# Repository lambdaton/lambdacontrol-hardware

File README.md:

# LambdaControl - Hardware Files

This repository contains design and hardware related files for my DIY MIDI controller project [LambdaControl](https://www.lambdaton.de/diy-hardware/lambda-control/).

I designed and build LambdaControl for my upcoming live performance and decided to release all components under open source licenses, such that other artists can use my project as they like.

A complete documentation of the project can be found on my [website](https://www.lambdaton.de/diy-hardware/lambda-control/).

## Project Overview
LambdaControl is based on the [MIDIbox project](http://www.ucapps.de/), which provides a complete solution for basic tasks like reading analog and digital inputs (faders, knobs and encoders). However, the RGB button matrix of LambdaControl, which works like the matrix of a Novation Launchpad, required a complete custom development.

LambdaControl consists of the following parts: components from the MIDIbox project for the basic I/O and USB MIDI connection, separate microcontroller which controls the RGB matrix, and a MIDI Remote Script that connects the controller with Ableton Live over USB. Additionally, I created this repository for the hardware parts like the RGB button matrix PCB or the 3D printable case.

## Faceplate

This folder contains the vector drawing for the faceplate of LambdaControl. I manufactured the faceplate with a professional laser cutter at the [Fab Lab Aachen](http://hci.rwth-aachen.de/fablab) out of 3mm acrylic glass. This drawing is especially designed for my used linear/rotary potentiometers and encoders, such that adjustments would be needed if you want to use other components. I have chosen rotary potentiometers and encoders that are mounted to the faceplate with a nut, since this provides a really strong connection. The linear potentiometers are connected to the faceplate with a screw.

## Button Matrix PCB

This folder contains the PCB that I designed for the RGB button matrix of LambdaControl. The [button pads](https://www.sparkfun.com/products/7835) that I used for the matrix are from Sparkfun, such that I also used parts from their [Sparkfun Eagle Library](https://github.com/sparkfun/SparkFun-Eagle-Libraries) to design the PCB.

The matrix consists of 60 pads (10 columns, 6 rows). Every pad contains a 5mm RGB LED for the feedback and contacts to detect button presses. Connecting all this LEDs and buttons directly would require to much I/O pins, such that the PCB is designed for multiplexing. Multiplexing dramatically reduces the necessary I/O pins by connecting the pads in a matrix, such that the microcontroller can frequently iterate over the pins for the columns and rows to detect button presses and turn the LEDs on. More information about the implementation of the multiplexing can be found in the documentation.

## Case

Since I recently started with 3D printing as a new hobby, I decided to build the case of LambdaControl by using a 3D printer. The case has a dimension of 416.4mm x 276.4mm and was designed with Fusion 360. Every standard FDM 3D printer should be able to print the case. I printed mine in PLA. The only problem is the large size of the case, since most printer can normally just print objects with a maximal size of 215mm x 215mm. Therefore, I cut the case into six parts that can be printed separately. The solid connection between the parts is achieved by tongue and groove joints in the walls and bottom (thanks to my friend Henning for the tip).

Moreover, the case contains several mounting points for the different parts of LambdaControl like the faceplate or the PCBs. These mounting points are implemented by standard brass injection molding inserts that allow to securely attach the PCBs to the case.

## Button Pad Spacer

This folder contains the 3D model of the Button Pad Spacer that I designed to clamp the Sparkfun [button pads](https://www.sparkfun.com/products/7835) onto my button matrix PCB.

# License
The Faceplate, Case, and Button Pad Spacers are licensed under the MIT license. The Button Matrix PCB is licensed under the Creative Commons ShareAlike 4.0 International license, since it is based on parts from the [Sparkfun Eagle Libary](https://github.com/sparkfun/SparkFun-Eagle-Libraries).

## Author

2017 - LambdaTon

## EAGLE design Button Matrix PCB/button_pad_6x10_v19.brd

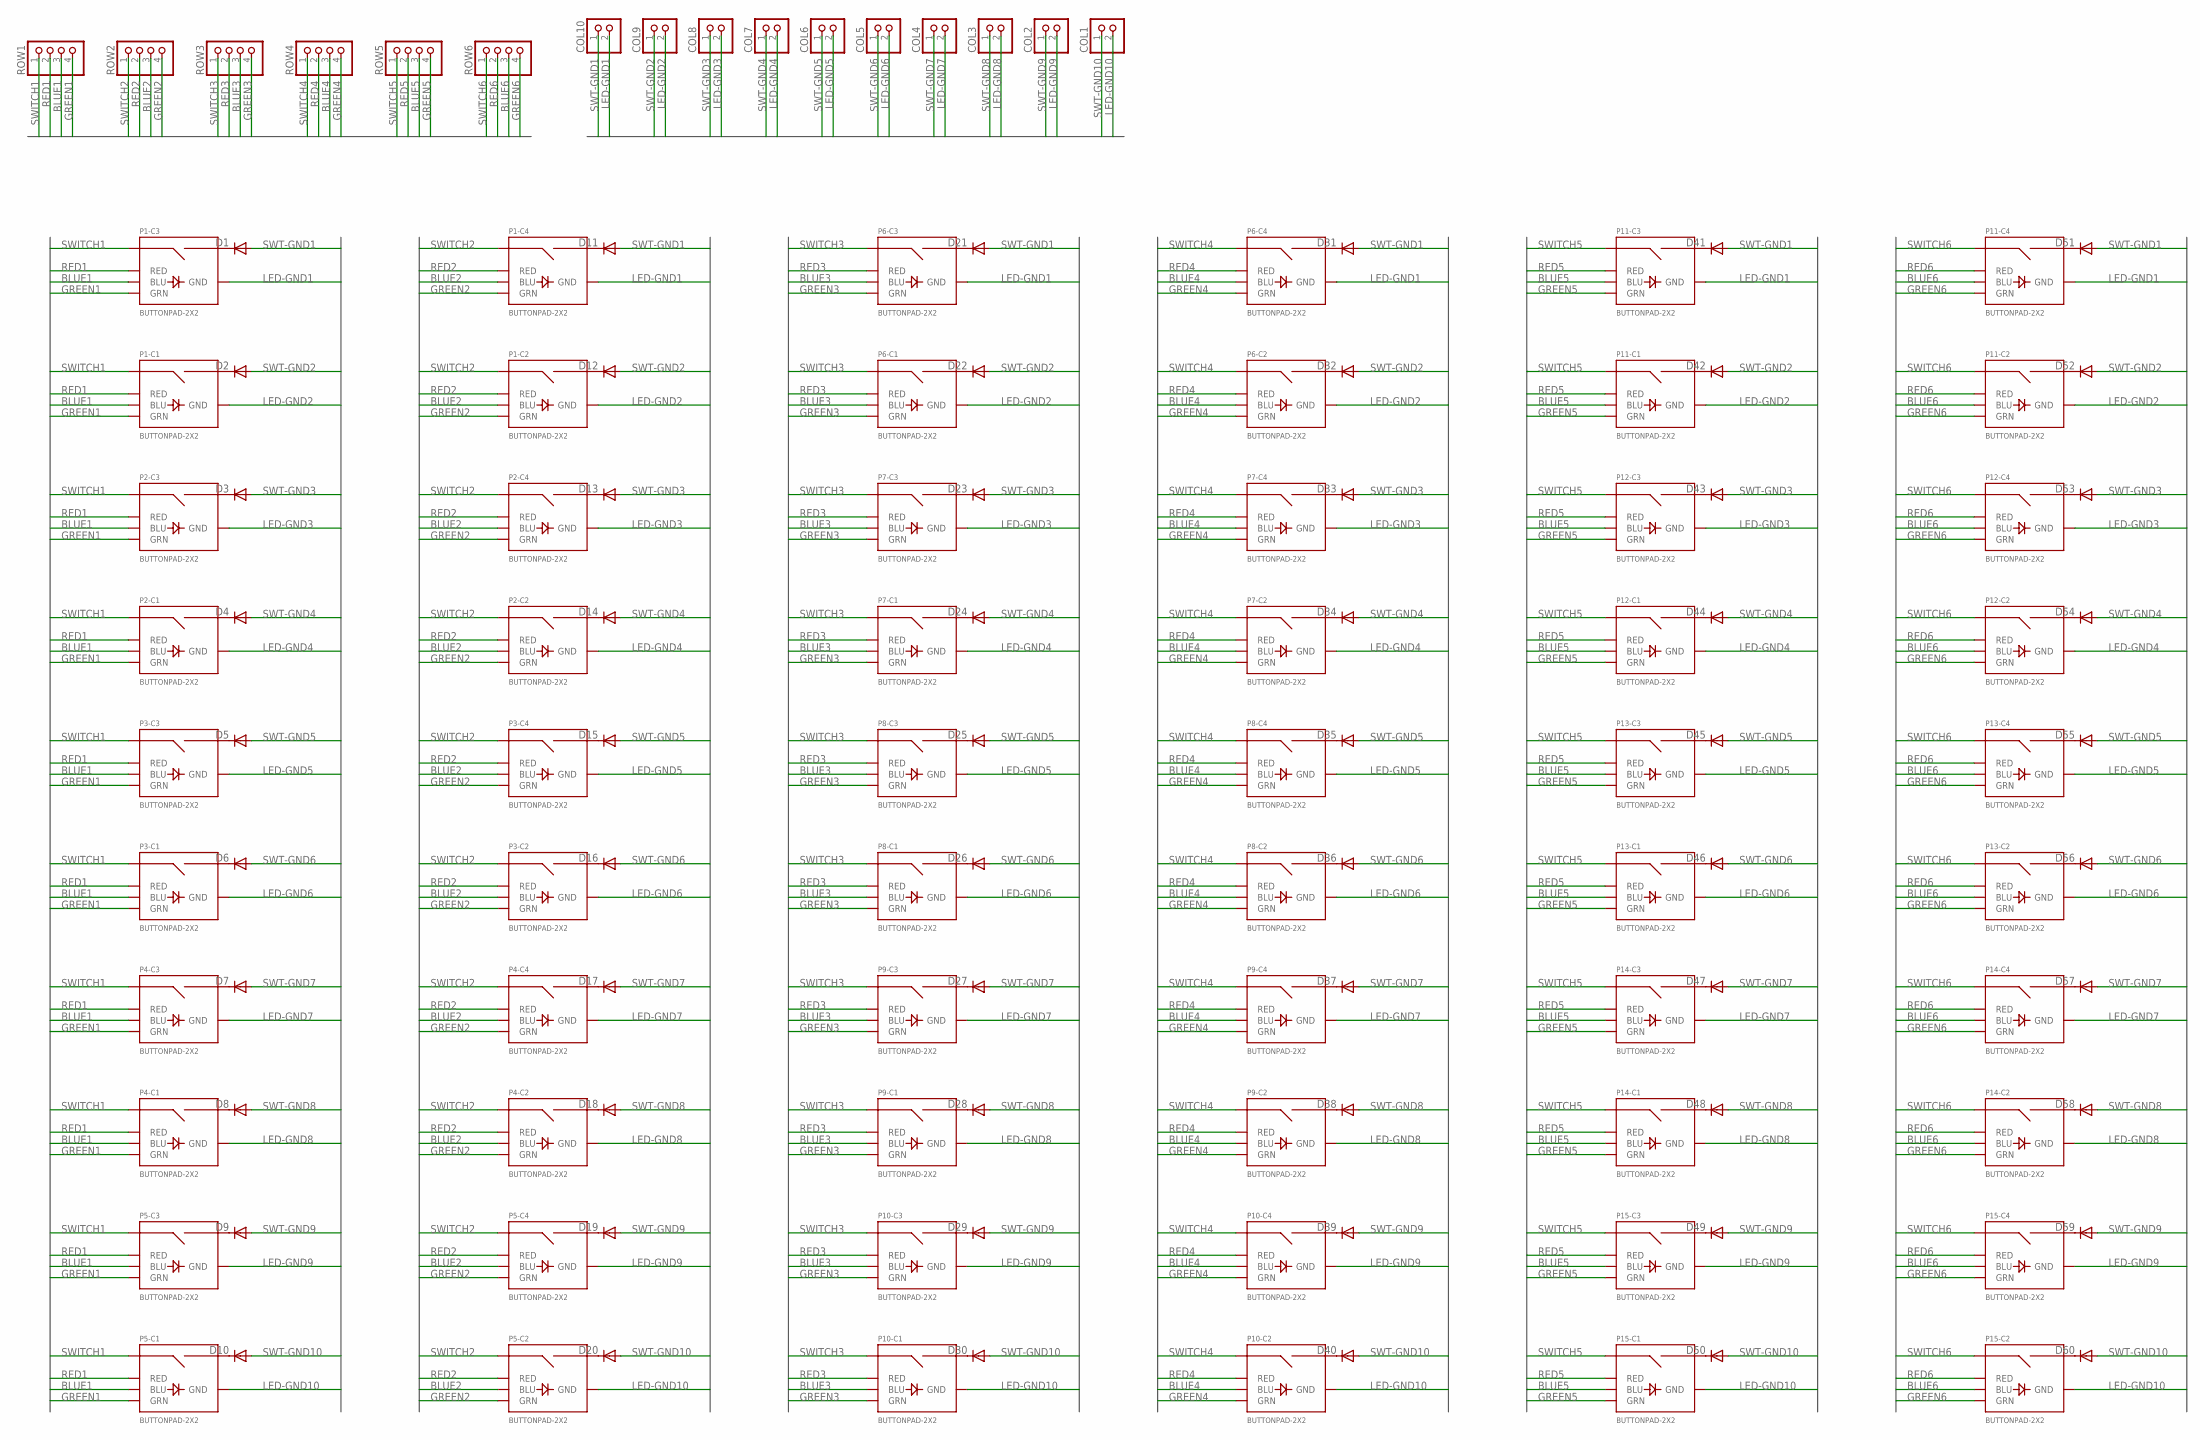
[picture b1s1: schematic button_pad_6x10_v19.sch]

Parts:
COL1, COL2, COL3, COL4, COL5, COL6, COL7, COL8, COL9, COL10: PINHD-1X2; 1X02
D1, D2, D3, D4, D5, D6, D7, D8, D9, D10, D11, D12, D13, D14, D15, D16, D17, D18, D19, D20, D21, D22, D23, D24, D25, D26, D27, D28, D29, D30, D31, D32, D33, D34, D35, D36, D37, D38, D39, D40, D41, D42, D43, D44, D45, D46, D47, D48, D49, D50, D51, D52, D53, D54, D55, D56, D57, D58, D59, D60: DIODE-1N4148; DOIDE-1N4148
P1, P2, P3, P4, P5, P6, P7, P8, P9, P10, P11, P12, P13, P14, P15: BUTTONPAD-2X2
ROW1, ROW2, ROW3, ROW4, ROW5, ROW6: PINHD-1X4; 1X04

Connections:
BLUE1: P1.BLU1 (BLU), P1.BLU3 (BLU), P2.BLU1 (BLU), P2.BLU3 (BLU), P3.BLU1 (BLU), P3.BLU3 (BLU), P4.BLU1 (BLU), P4.BLU3 (BLU), P5.BLU1 (BLU), P5.BLU3 (BLU), ROW1.3
BLUE2: P1.BLU2 (BLU), P1.BLU4 (BLU), P2.BLU2 (BLU), P2.BLU4 (BLU), P3.BLU2 (BLU), P3.BLU4 (BLU), P4.BLU2 (BLU), P4.BLU4 (BLU), P5.BLU2 (BLU), P5.BLU4 (BLU), ROW2.3
BLUE3: P6.BLU1 (BLU), P6.BLU3 (BLU), P7.BLU1 (BLU), P7.BLU3 (BLU), P8.BLU1 (BLU), P8.BLU3 (BLU), P9.BLU1 (BLU), P9.BLU3 (BLU), P10.BLU1 (BLU), P10.BLU3 (BLU), ROW3.3
BLUE4: P6.BLU2 (BLU), P6.BLU4 (BLU), P7.BLU2 (BLU), P7.BLU4 (BLU), P8.BLU2 (BLU), P8.BLU4 (BLU), P9.BLU2 (BLU), P9.BLU4 (BLU), P10.BLU2 (BLU), P10.BLU4 (BLU), ROW4.3
BLUE5: P11.BLU1 (BLU), P11.BLU3 (BLU), P12.BLU1 (BLU), P12.BLU3 (BLU), P13.BLU1 (BLU), P13.BLU3 (BLU), P14.BLU1 (BLU), P14.BLU3 (BLU), P15.BLU1 (BLU), P15.BLU3 (BLU), ROW5.3
BLUE6: P11.BLU2 (BLU), P11.BLU4 (BLU), P12.BLU2 (BLU), P12.BLU4 (BLU), P13.BLU2 (BLU), P13.BLU4 (BLU), P14.BLU2 (BLU), P14.BLU4 (BLU), P15.BLU2 (BLU), P15.BLU4 (BLU), ROW6.3
GREEN1: P1.GRN1 (GRN), P1.GRN3 (GRN), P2.GRN1 (GRN), P2.GRN3 (GRN), P3.GRN1 (GRN), P3.GRN3 (GRN), P4.GRN1 (GRN), P4.GRN3 (GRN), P5.GRN1 (GRN), P5.GRN3 (GRN), ROW1.4
GREEN2: P1.GRN2 (GRN), P1.GRN4 (GRN), P2.GRN2 (GRN), P2.GRN4 (GRN), P3.GRN2 (GRN), P3.GRN4 (GRN), P4.GRN2 (GRN), P4.GRN4 (GRN), P5.GRN2 (GRN), P5.GRN4 (GRN), ROW2.4
GREEN3: P6.GRN1 (GRN), P6.GRN3 (GRN), P7.GRN1 (GRN), P7.GRN3 (GRN), P8.GRN1 (GRN), P8.GRN3 (GRN), P9.GRN1 (GRN), P9.GRN3 (GRN), P10.GRN1 (GRN), P10.GRN3 (GRN), ROW3.4
GREEN4: P6.GRN2 (GRN), P6.GRN4 (GRN), P7.GRN2 (GRN), P7.GRN4 (GRN), P8.GRN2 (GRN), P8.GRN4 (GRN), P9.GRN2 (GRN), P9.GRN4 (GRN), P10.GRN2 (GRN), P10.GRN4 (GRN), ROW4.4
GREEN5: P11.GRN1 (GRN), P11.GRN3 (GRN), P12.GRN1 (GRN), P12.GRN3 (GRN), P13.GRN1 (GRN), P13.GRN3 (GRN), P14.GRN1 (GRN), P14.GRN3 (GRN), P15.GRN1 (GRN), P15.GRN3 (GRN), ROW5.4
GREEN6: P11.GRN2 (GRN), P11.GRN4 (GRN), P12.GRN2 (GRN), P12.GRN4 (GRN), P13.GRN2 (GRN), P13.GRN4 (GRN), P14.GRN2 (GRN), P14.GRN4 (GRN), P15.GRN2 (GRN), P15.GRN4 (GRN), ROW6.4
LED-GND1: COL10.2, P1.GND3 (GND), P1.GND4 (GND), P6.GND3 (GND), P6.GND4 (GND), P11.GND3 (GND), P11.GND4 (GND)
LED-GND2: COL9.2, P1.GND1 (GND), P1.GND2 (GND), P6.GND1 (GND), P6.GND2 (GND), P11.GND1 (GND), P11.GND2 (GND)
LED-GND3: COL8.2, P2.GND3 (GND), P2.GND4 (GND), P7.GND3 (GND), P7.GND4 (GND), P12.GND3 (GND), P12.GND4 (GND)
LED-GND4: COL7.2, P2.GND1 (GND), P2.GND2 (GND), P7.GND1 (GND), P7.GND2 (GND), P12.GND1 (GND), P12.GND2 (GND)
LED-GND5: COL6.2, P3.GND3 (GND), P3.GND4 (GND), P8.GND3 (GND), P8.GND4 (GND), P13.GND3 (GND), P13.GND4 (GND)
LED-GND6: COL5.2, P3.GND1 (GND), P3.GND2 (GND), P8.GND1 (GND), P8.GND2 (GND), P13.GND1 (GND), P13.GND2 (GND)
LED-GND7: COL4.2, P4.GND3 (GND), P4.GND4 (GND), P9.GND3 (GND), P9.GND4 (GND), P14.GND3 (GND), P14.GND4 (GND)
LED-GND8: COL3.2, P4.GND1 (GND), P4.GND2 (GND), P9.GND1 (GND), P9.GND2 (GND), P14.GND1 (GND), P14.GND2 (GND)
LED-GND9: COL2.2, P5.GND3 (GND), P5.GND4 (GND), P10.GND3 (GND), P10.GND4 (GND), P15.GND3 (GND), P15.GND4 (GND)
LED-GND10: COL1.2, P5.GND1 (GND), P5.GND2 (GND), P10.GND1 (GND), P10.GND2 (GND), P15.GND1 (GND), P15.GND2 (GND)
unnamed: D1.P$2 (C), P1.SIG6 (SIG2)
unnamed: D2.P$2 (C), P1.SIG2
unnamed: D3.P$2 (C), P2.SIG6 (SIG2)
unnamed: D4.P$2 (C), P2.SIG2
unnamed: D5.P$2 (C), P3.SIG6 (SIG2)
unnamed: D6.P$2 (C), P3.SIG2
unnamed: D16.P$2 (C), P3.SIG4 (SIG2)
unnamed: D15.P$2 (C), P3.SIG8 (SIG2)
unnamed: D14.P$2 (C), P2.SIG4 (SIG2)
unnamed: D13.P$2 (C), P2.SIG8 (SIG2)
unnamed: D12.P$2 (C), P1.SIG4 (SIG2)
unnamed: D11.P$2 (C), P1.SIG8 (SIG2)
unnamed: D7.P$2 (C), P4.SIG6 (SIG2)
unnamed: D8.P$2 (C), P4.SIG2
unnamed: D9.P$2 (C), P5.SIG6 (SIG2)
unnamed: D10.P$2 (C), P5.SIG2
unnamed: D21.P$2 (C), P6.SIG6 (SIG2)
unnamed: D22.P$2 (C), P6.SIG2
unnamed: D32.P$2 (C), P6.SIG4 (SIG2)
unnamed: D31.P$2 (C), P6.SIG8 (SIG2)
unnamed: D20.P$2 (C), P5.SIG4 (SIG2)
unnamed: D19.P$2 (C), P5.SIG8 (SIG2)
unnamed: D18.P$2 (C), P4.SIG4 (SIG2)
unnamed: D17.P$2 (C), P4.SIG8 (SIG2)
unnamed: D23.P$2 (C), P7.SIG6 (SIG2)
unnamed: D24.P$2 (C), P7.SIG2
unnamed: D33.P$2 (C), P7.SIG8 (SIG2)
unnamed: D34.P$2 (C), P7.SIG4 (SIG2)
unnamed: D30.P$2 (C), P10.SIG2
unnamed: D29.P$2 (C), P10.SIG6 (SIG2)
unnamed: D39.P$2 (C), P10.SIG8 (SIG2)
unnamed: D40.P$2 (C), P10.SIG4 (SIG2)
unnamed: D46.P$2 (C), P13.SIG2
unnamed: D45.P$2 (C), P13.SIG6 (SIG2)
unnamed: D55.P$2 (C), P13.SIG8 (SIG2)
unnamed: D56.P$2 (C), P13.SIG4 (SIG2)
unnamed: D47.P$2 (C), P14.SIG6 (SIG2)
unnamed: D48.P$2 (C), P14.SIG2
unnamed: D58.P$2 (C), P14.SIG4 (SIG2)
unnamed: D57.P$2 (C), P14.SIG8 (SIG2)
unnamed: D51.P$2 (C), P11.SIG8 (SIG2)
unnamed: D41.P$2 (C), P11.SIG6 (SIG2)
unnamed: D42.P$2 (C), P11.SIG2
unnamed: D52.P$2 (C), P11.SIG4 (SIG2)
unnamed: D25.P$2 (C), P8.SIG6 (SIG2)
unnamed: D35.P$2 (C), P8.SIG8 (SIG2)
unnamed: D36.P$2 (C), P8.SIG4 (SIG2)
unnamed: D26.P$2 (C), P8.SIG2
unnamed: D27.P$2 (C), P9.SIG6 (SIG2)
unnamed: D28.P$2 (C), P9.SIG2
unnamed: D37.P$2 (C), P9.SIG8 (SIG2)
unnamed: D38.P$2 (C), P9.SIG4 (SIG2)
unnamed: D43.P$2 (C), P12.SIG6 (SIG2)
unnamed: D44.P$2 (C), P12.SIG2
unnamed: D53.P$2 (C), P12.SIG8 (SIG2)
unnamed: D54.P$2 (C), P12.SIG4 (SIG2)
unnamed: D50.P$2 (C), P15.SIG2
unnamed: D49.P$2 (C), P15.SIG6 (SIG2)
unnamed: D59.P$2 (C), P15.SIG8 (SIG2)
unnamed: D60.P$2 (C), P15.SIG4 (SIG2)
RED1: P1.RED1 (RED), P1.RED3 (RED), P2.RED1 (RED), P2.RED3 (RED), P3.RED1 (RED), P3.RED3 (RED), P4.RED1 (RED), P4.RED3 (RED), P5.RED1 (RED), P5.RED3 (RED), ROW1.2
RED2: P1.RED2 (RED), P1.RED4 (RED), P2.RED2 (RED), P2.RED4 (RED), P3.RED2 (RED), P3.RED4 (RED), P4.RED2 (RED), P4.RED4 (RED), P5.RED2 (RED), P5.RED4 (RED), ROW2.2
RED3: P6.RED1 (RED), P6.RED3 (RED), P7.RED1 (RED), P7.RED3 (RED), P8.RED1 (RED), P8.RED3 (RED), P9.RED1 (RED), P9.RED3 (RED), P10.RED1 (RED), P10.RED3 (RED), ROW3.2
RED4: P6.RED2 (RED), P6.RED4 (RED), P7.RED2 (RED), P7.RED4 (RED), P8.RED2 (RED), P8.RED4 (RED), P9.RED2 (RED), P9.RED4 (RED), P10.RED2 (RED), P10.RED4 (RED), ROW4.2
RED5: P11.RED1 (RED), P11.RED3 (RED), P12.RED1 (RED), P12.RED3 (RED), P13.RED1 (RED), P13.RED3 (RED), P14.RED1 (RED), P14.RED3 (RED), P15.RED1 (RED), P15.RED3 (RED), ROW5.2
RED6: P11.RED2 (RED), P11.RED4 (RED), P12.RED2 (RED), P12.RED4 (RED), P13.RED2 (RED), P13.RED4 (RED), P14.RED2 (RED), P14.RED4 (RED), P15.RED2 (RED), P15.RED4 (RED), ROW6.2
SWITCH1: P1.SIG1, P1.SIG5 (SIG1), P2.SIG1, P2.SIG5 (SIG1), P3.SIG1, P3.SIG5 (SIG1), P4.SIG1, P4.SIG5 (SIG1), P5.SIG1, P5.SIG5 (SIG1), ROW1.1
SWITCH2: P1.SIG3 (SIG1), P1.SIG7 (SIG1), P2.SIG3 (SIG1), P2.SIG7 (SIG1), P3.SIG3 (SIG1), P3.SIG7 (SIG1), P4.SIG3 (SIG1), P4.SIG7 (SIG1), P5.SIG3 (SIG1), P5.SIG7 (SIG1), ROW2.1
SWITCH3: P6.SIG1, P6.SIG5 (SIG1), P7.SIG1, P7.SIG5 (SIG1), P8.SIG1, P8.SIG5 (SIG1), P9.SIG1, P9.SIG5 (SIG1), P10.SIG1, P10.SIG5 (SIG1), ROW3.1
SWITCH4: P6.SIG3 (SIG1), P6.SIG7 (SIG1), P7.SIG3 (SIG1), P7.SIG7 (SIG1), P8.SIG3 (SIG1), P8.SIG7 (SIG1), P9.SIG3 (SIG1), P9.SIG7 (SIG1), P10.SIG3 (SIG1), P10.SIG7 (SIG1), ROW4.1
SWITCH5: P11.SIG1, P11.SIG5 (SIG1), P12.SIG1, P12.SIG5 (SIG1), P13.SIG1, P13.SIG5 (SIG1), P14.SIG1, P14.SIG5 (SIG1), P15.SIG1, P15.SIG5 (SIG1), ROW5.1
SWITCH6: P11.SIG3 (SIG1), P11.SIG7 (SIG1), P12.SIG3 (SIG1), P12.SIG7 (SIG1), P13.SIG3 (SIG1), P13.SIG7 (SIG1), P14.SIG3 (SIG1), P14.SIG7 (SIG1), P15.SIG3 (SIG1), P15.SIG7 (SIG1), ROW6.1
SWT-GND1: COL10.1, D1.P$1 (A), D11.P$1 (A), D21.P$1 (A), D31.P$1 (A), D41.P$1 (A), D51.P$1 (A)
SWT-GND2: COL9.1, D2.P$1 (A), D12.P$1 (A), D22.P$1 (A), D32.P$1 (A), D42.P$1 (A), D52.P$1 (A)
SWT-GND3: COL8.1, D3.P$1 (A), D13.P$1 (A), D23.P$1 (A), D33.P$1 (A), D43.P$1 (A), D53.P$1 (A)
SWT-GND4: COL7.1, D4.P$1 (A), D14.P$1 (A), D24.P$1 (A), D34.P$1 (A), D44.P$1 (A), D54.P$1 (A)
SWT-GND5: COL6.1, D5.P$1 (A), D15.P$1 (A), D25.P$1 (A), D35.P$1 (A), D45.P$1 (A), D55.P$1 (A)
SWT-GND6: COL5.1, D6.P$1 (A), D16.P$1 (A), D26.P$1 (A), D36.P$1 (A), D46.P$1 (A), D56.P$1 (A)
SWT-GND7: COL4.1, D7.P$1 (A), D17.P$1 (A), D27.P$1 (A), D37.P$1 (A), D47.P$1 (A), D57.P$1 (A)
SWT-GND8: COL3.1, D8.P$1 (A), D18.P$1 (A), D28.P$1 (A), D38.P$1 (A), D48.P$1 (A), D58.P$1 (A)
SWT-GND9: COL2.1, D9.P$1 (A), D19.P$1 (A), D29.P$1 (A), D39.P$1 (A), D49.P$1 (A), D59.P$1 (A)
SWT-GND10: COL1.1, D10.P$1 (A), D20.P$1 (A), D30.P$1 (A), D40.P$1 (A), D50.P$1 (A), D60.P$1 (A)

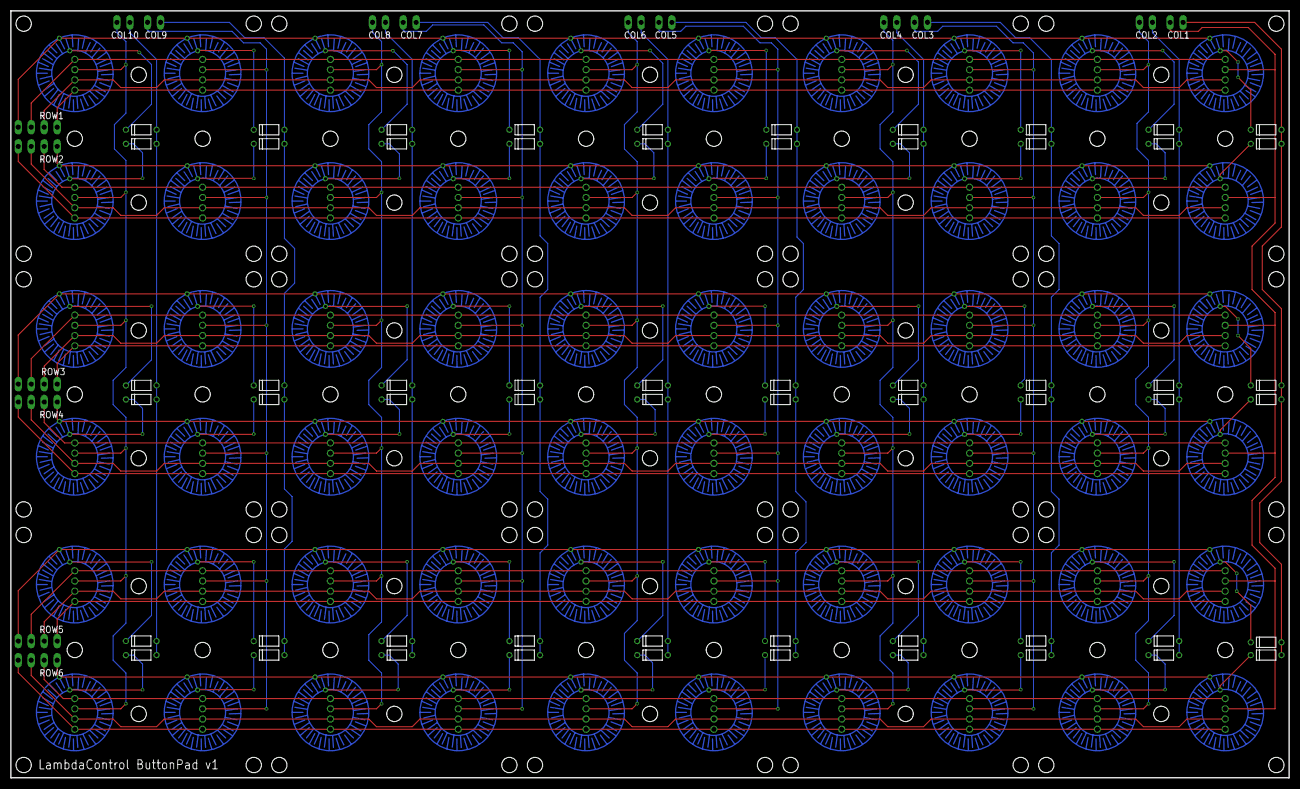
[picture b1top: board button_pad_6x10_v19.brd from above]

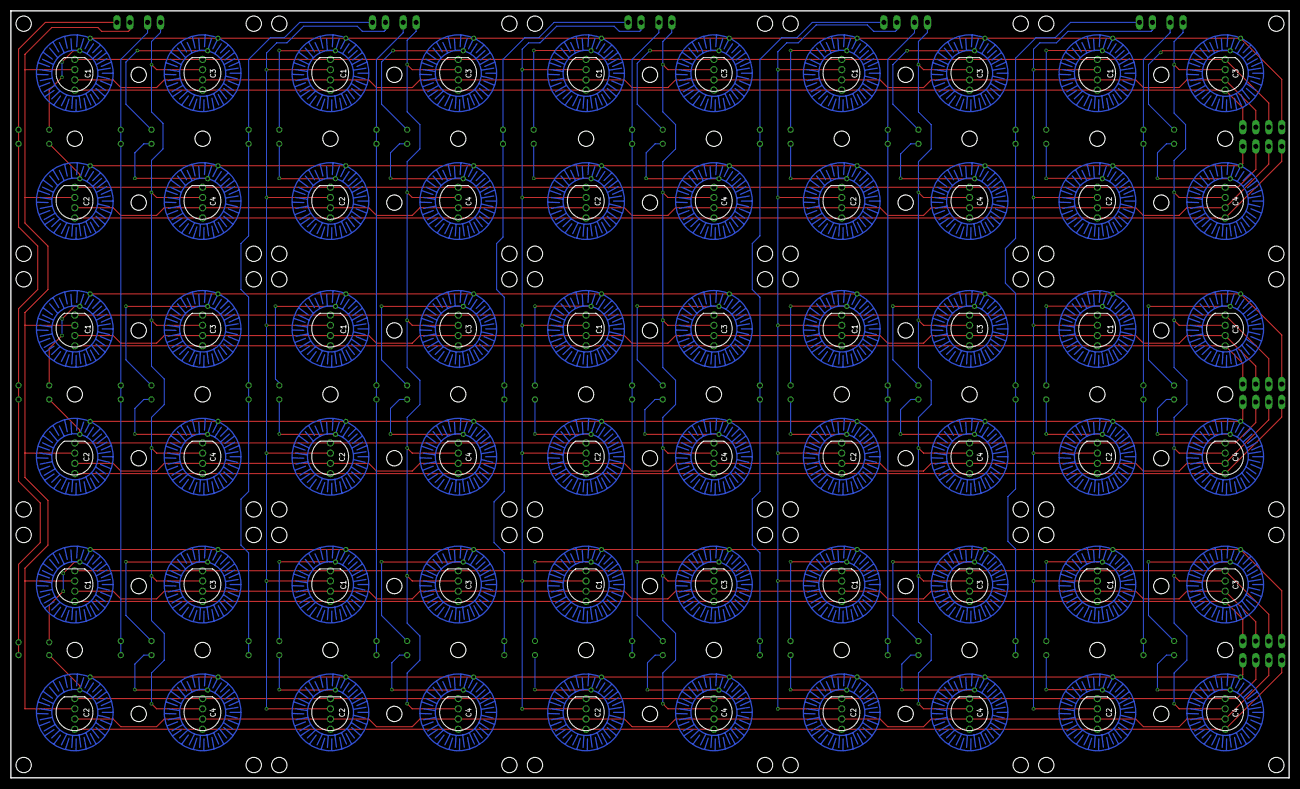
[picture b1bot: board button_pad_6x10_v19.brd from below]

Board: 2 copper layers, 250.0 x 150.0 mm, 91 parts (15 on the bottom side), 104 nets.

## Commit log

2017-12-17 Release version 1.0

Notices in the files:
parts and their libraries:
SparkFun-Electromechanical: Licensing: Creative Commons ShareAlike 4.0 International - https://creativecommons.org/licenses/by-sa/4.0
